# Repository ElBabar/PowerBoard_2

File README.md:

# PowerBoard_2

KiCad Rackable Power Board for my Robotics club robot, taking part in the Coupe de France de Robotique.

BOM is to come.	

You might need to use my library:
add https://github.com/ElBabar/Libabar.git
to your KiCad paths.

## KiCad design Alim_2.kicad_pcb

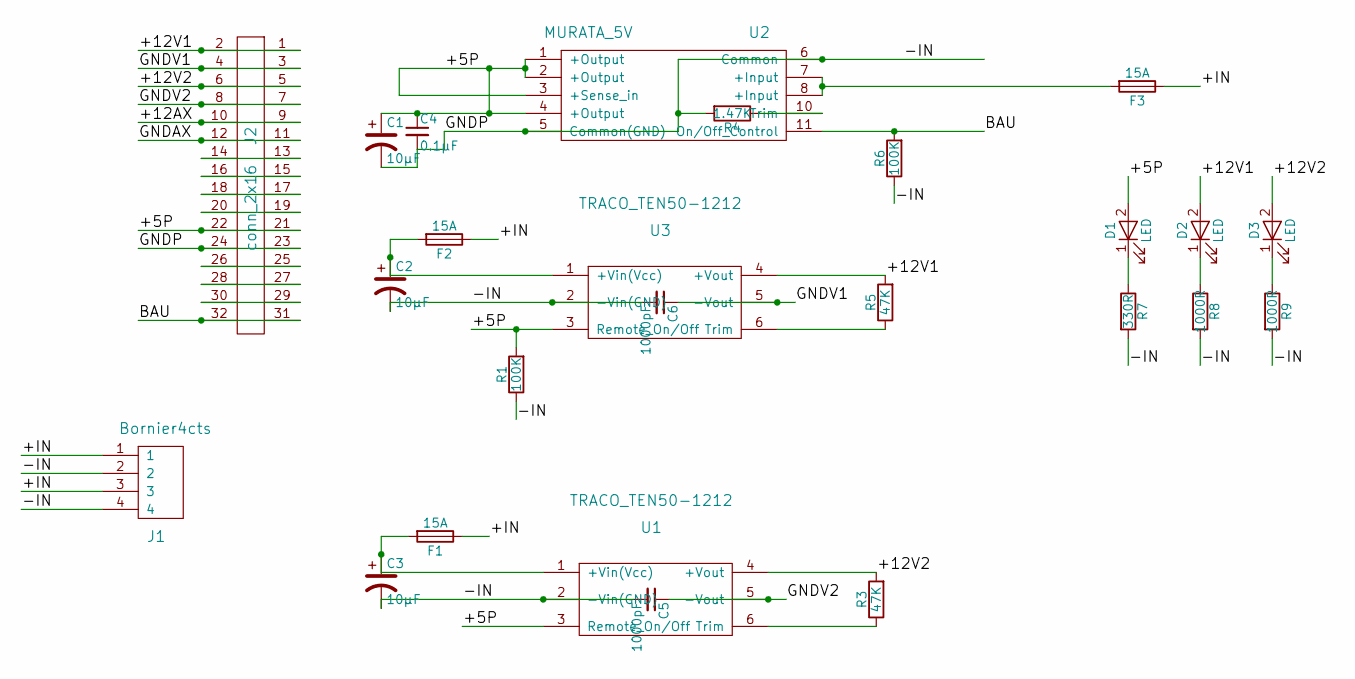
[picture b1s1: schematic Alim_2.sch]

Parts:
C1, C2, C3: 10µF; CP_Radial_D5.0mm_P2.50mm
C4: 0.1µF; C_Disc_D3.8mm_W2.6mm_P2.50mm
C5, C6: 1000pF; C_Disc_D3.8mm_W2.6mm_P2.50mm
D1, D2, D3: LED; LED_D3.0mm
F1, F2, F3: 15A; Fuseholder5x20_horiz_open_universal_Type-III
J1: Bornier4cts
J2: conn_2x16
R1, R6: 100K; R_Axial_DIN0207_L6.3mm_D2.5mm_P10.16mm_Horizontal
R3, R5: 47K; R_Axial_DIN0207_L6.3mm_D2.5mm_P10.16mm_Horizontal
R4: 1.47K; R_Axial_DIN0207_L6.3mm_D2.5mm_P10.16mm_Horizontal
R7: 330R; R_Axial_DIN0207_L6.3mm_D2.5mm_P10.16mm_Horizontal
R8, R9: 1000R; R_Axial_DIN0207_L6.3mm_D2.5mm_P10.16mm_Horizontal
U1, U3: TRACO_TEN50-1212
U2: MURATA_5V

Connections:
/+5P: C1.1, C4.1, D1.2 (A), J2.21, J2.22, R1.2, U1.3 (Remote_On/Off), U2.1 (+Output), U2.2 (+Output), U2.3 (+Sense_in), U2.4 (+Output), U3.3 (Remote_On/Off)
/+12AX: J2.9, J2.10
/+12V1: D2.2 (A), J2.1, J2.2, R5.2, U3.4 (+Vout)
/+12V2: D3.2 (A), J2.5, J2.6, R3.2, U1.4 (+Vout)
/+IN: F1.1, F2.1, F3.1, J1.1, J1.3
/-IN: C1.2, C2.2, C3.2, C4.2, C5.2, C6.2, J1.2, J1.4, J2.23, J2.24, R1.1, R4.2, R6.1, R7.2, R8.2, R9.2, U1.2 (-Vin(GND)), U2.5 (Common(GND)), U2.6 (Common), U3.2 (-Vin(GND))
/BAU: J2.31, J2.32, R6.2, U2.11 (On/Off_Control)
/GNDAX: J2.11, J2.12
/GNDV1: C6.1, J2.3, J2.4, U3.5 (-Vout)
/GNDV2: C5.1, J2.7, J2.8, U1.5 (-Vout)
unnamed: C2.1, F2.2, U3.1 (+Vin(Vcc))
unnamed: C3.1, F1.2, U1.1 (+Vin(Vcc))
unnamed: D1.1 (K), R7.1
unnamed: D2.1 (K), R8.1
unnamed: D3.1 (K), R9.1
unnamed: F3.2, U2.7 (+Input), U2.8 (+Input)
unnamed: J2.13, J2.14
unnamed: J2.15, J2.16
unnamed: J2.17, J2.18
unnamed: J2.19, J2.20
unnamed: J2.25, J2.26
unnamed: J2.27, J2.28
unnamed: J2.29, J2.30
unnamed: R3.1, U1.6 (Trim)
unnamed: R4.1, U2.10 (Trim)
unnamed: R5.1, U3.6 (Trim)

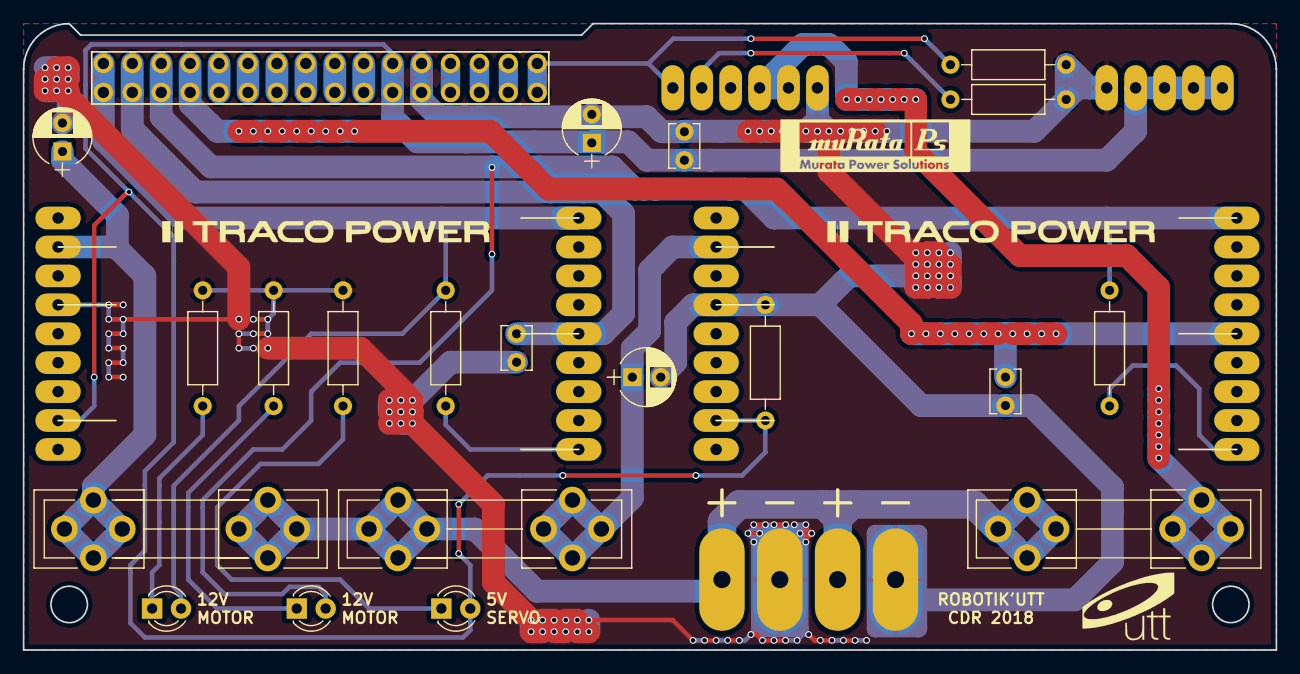
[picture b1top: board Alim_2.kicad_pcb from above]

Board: 2 copper layers, 110.0 x 55.0 mm, 25 parts (0 on the bottom side), 26 nets.

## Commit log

2018-02-07 minor changes
2018-02-07 added generated gerber
